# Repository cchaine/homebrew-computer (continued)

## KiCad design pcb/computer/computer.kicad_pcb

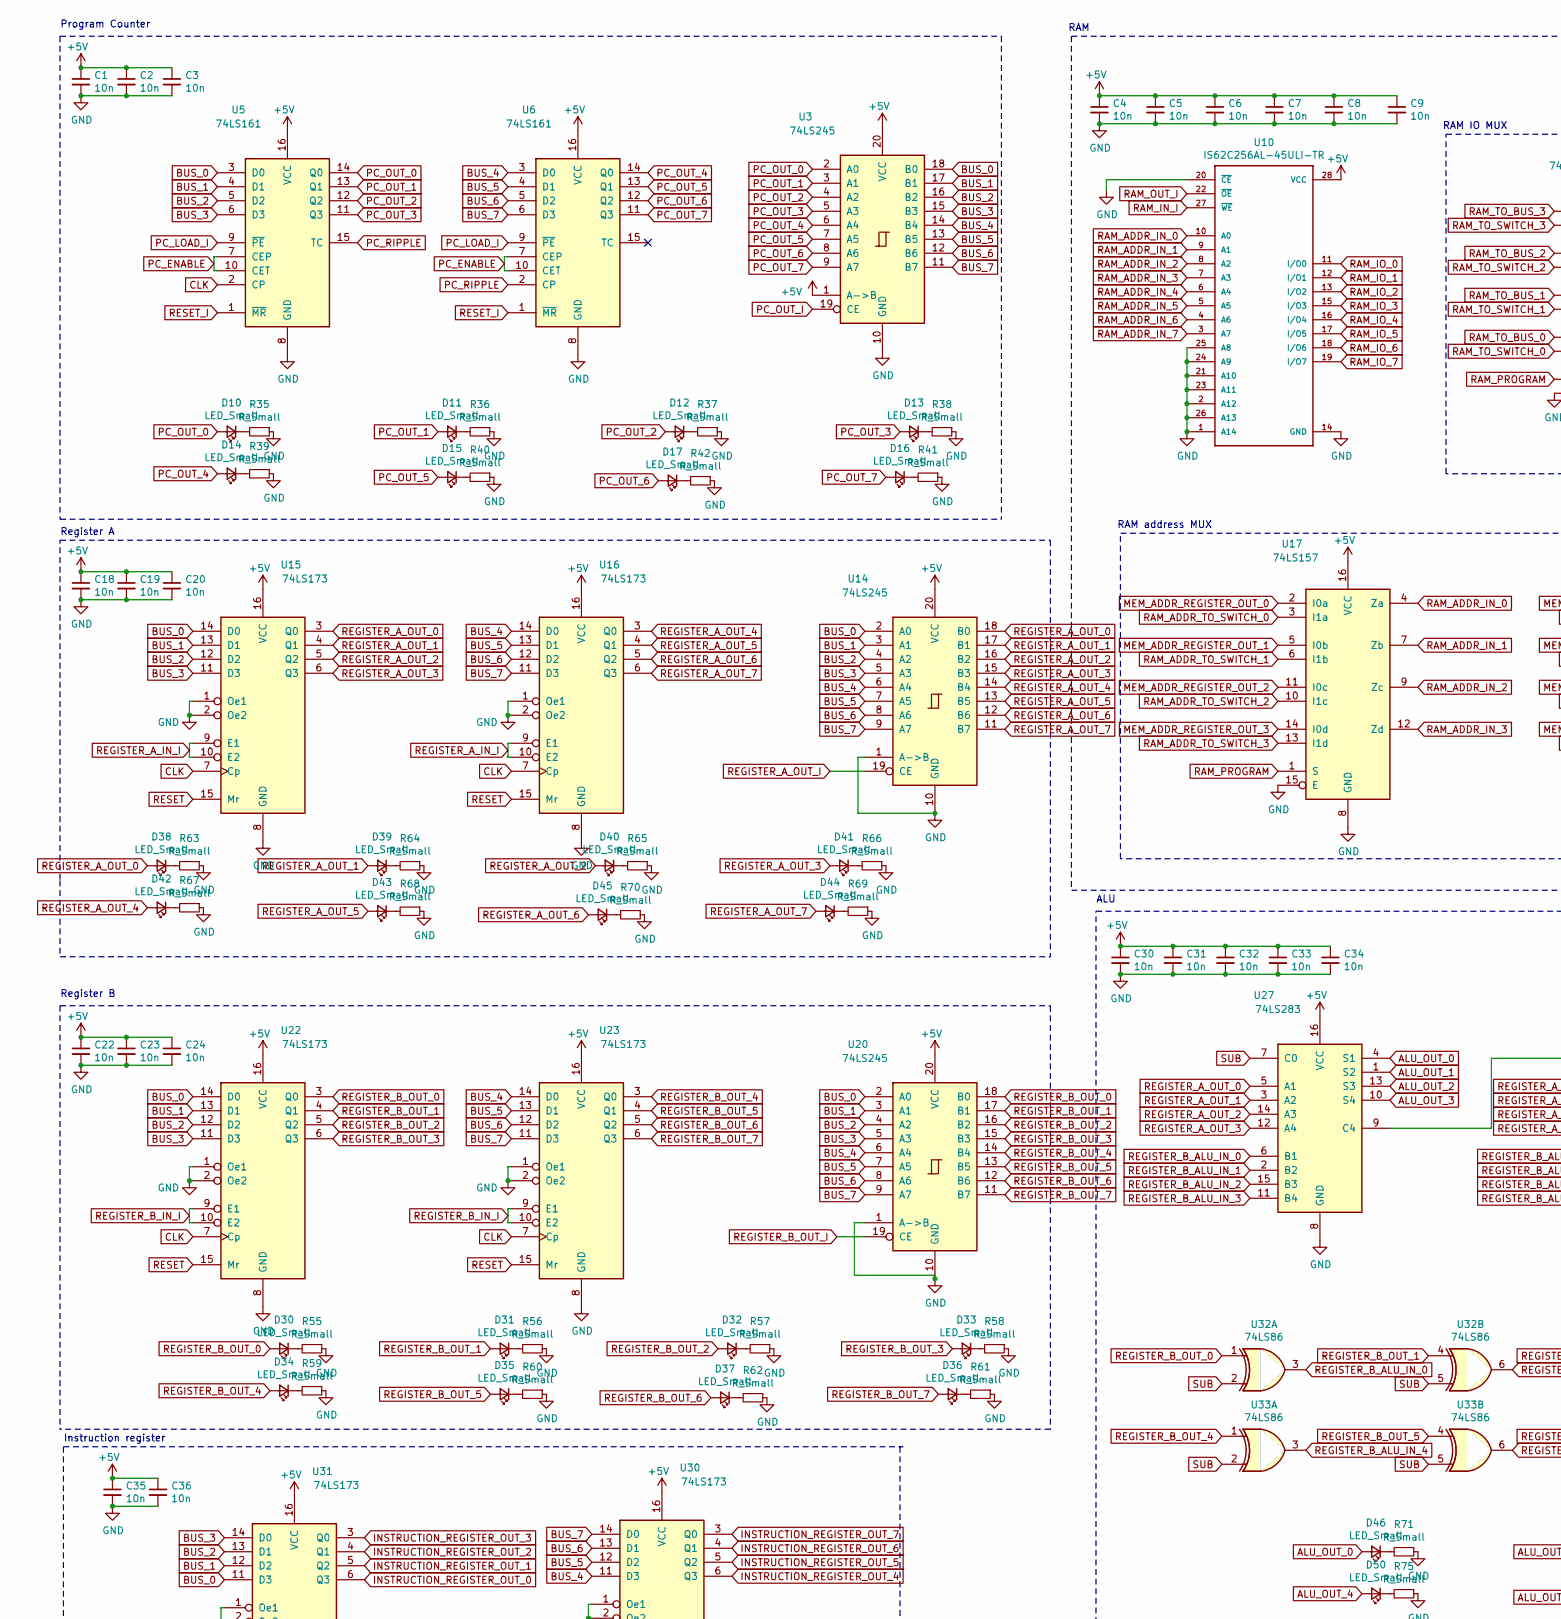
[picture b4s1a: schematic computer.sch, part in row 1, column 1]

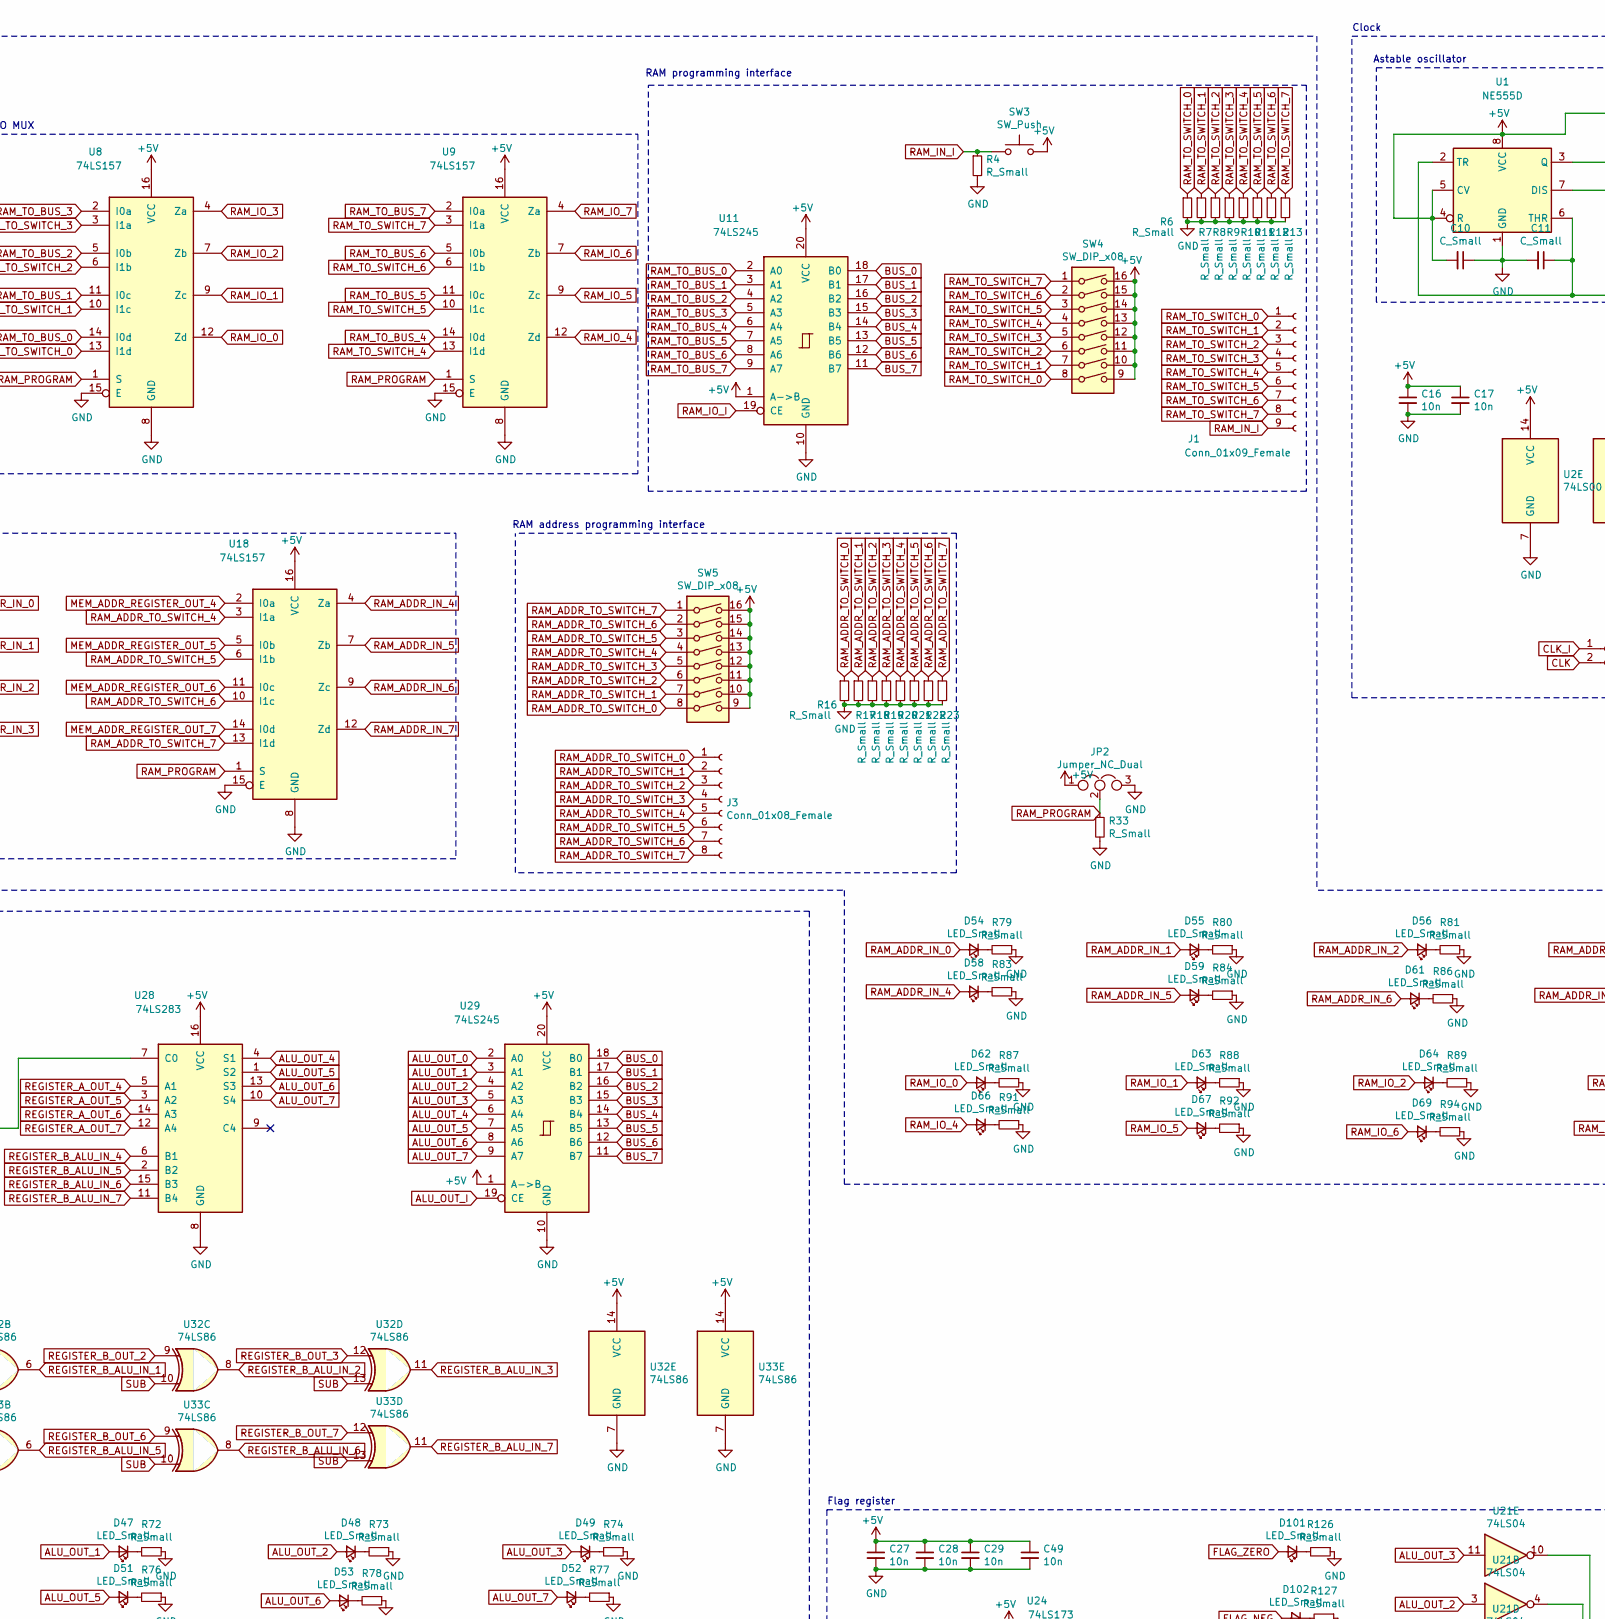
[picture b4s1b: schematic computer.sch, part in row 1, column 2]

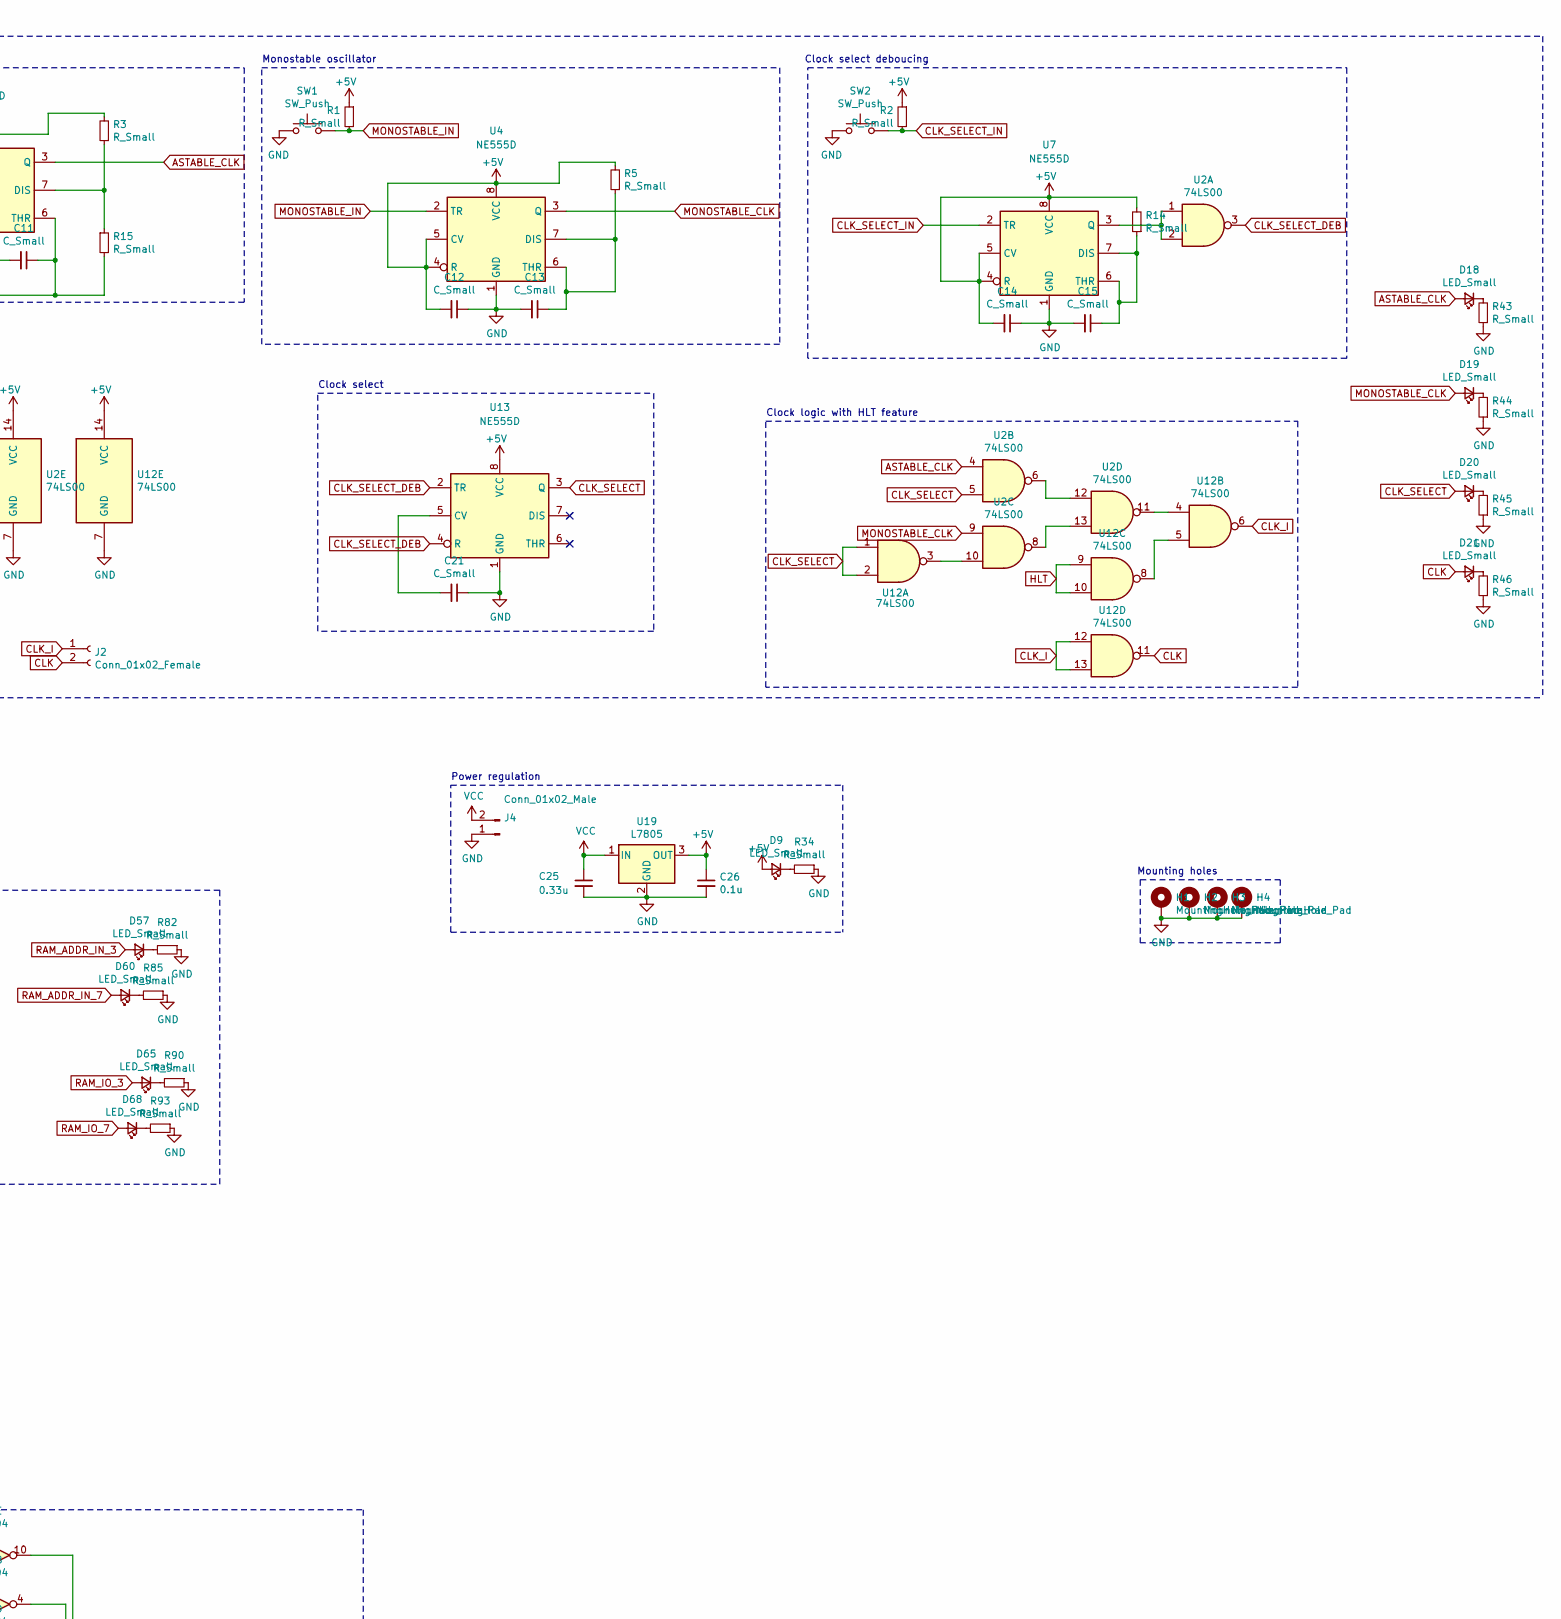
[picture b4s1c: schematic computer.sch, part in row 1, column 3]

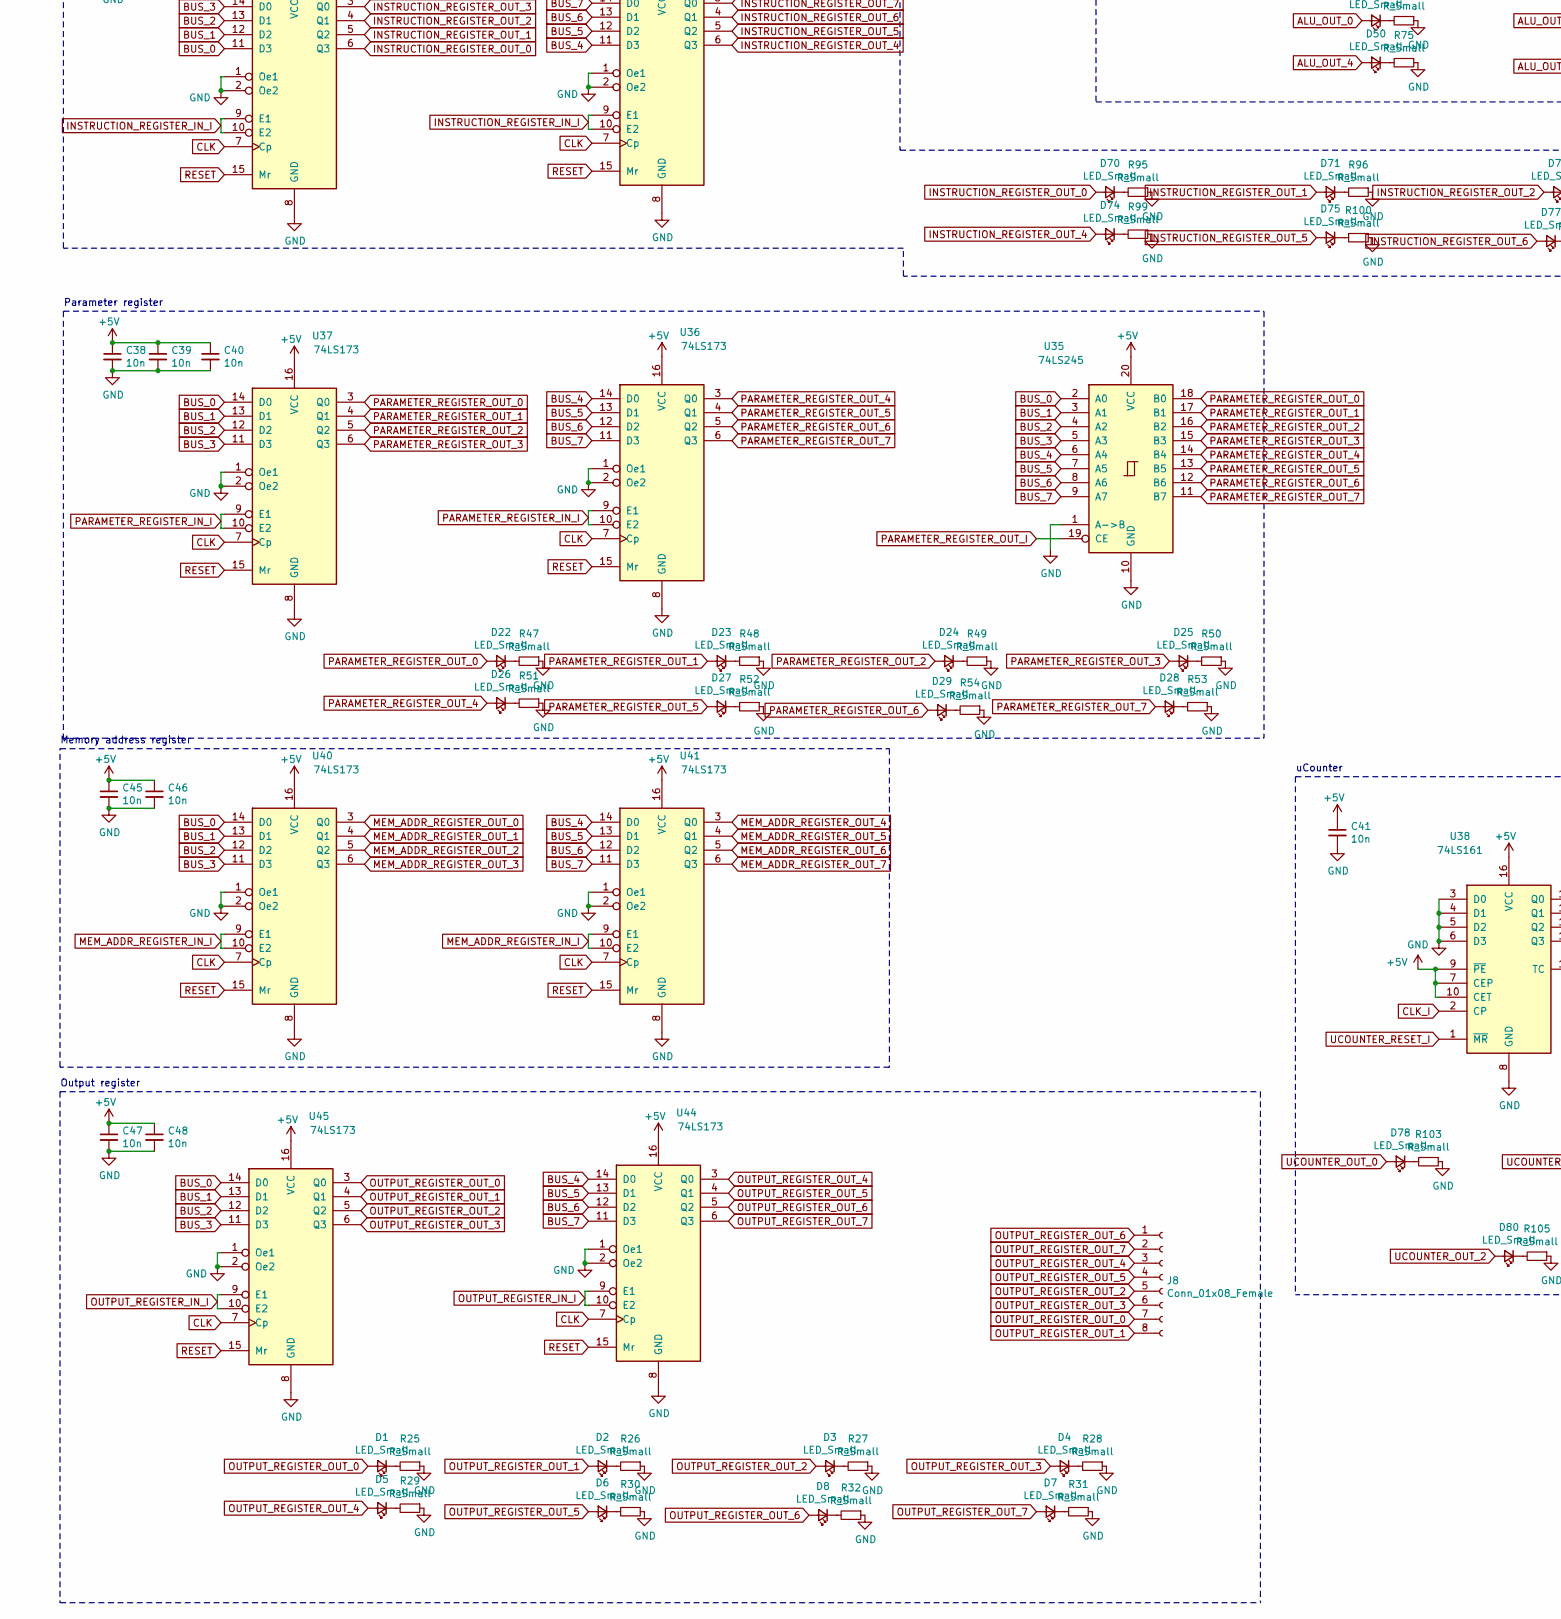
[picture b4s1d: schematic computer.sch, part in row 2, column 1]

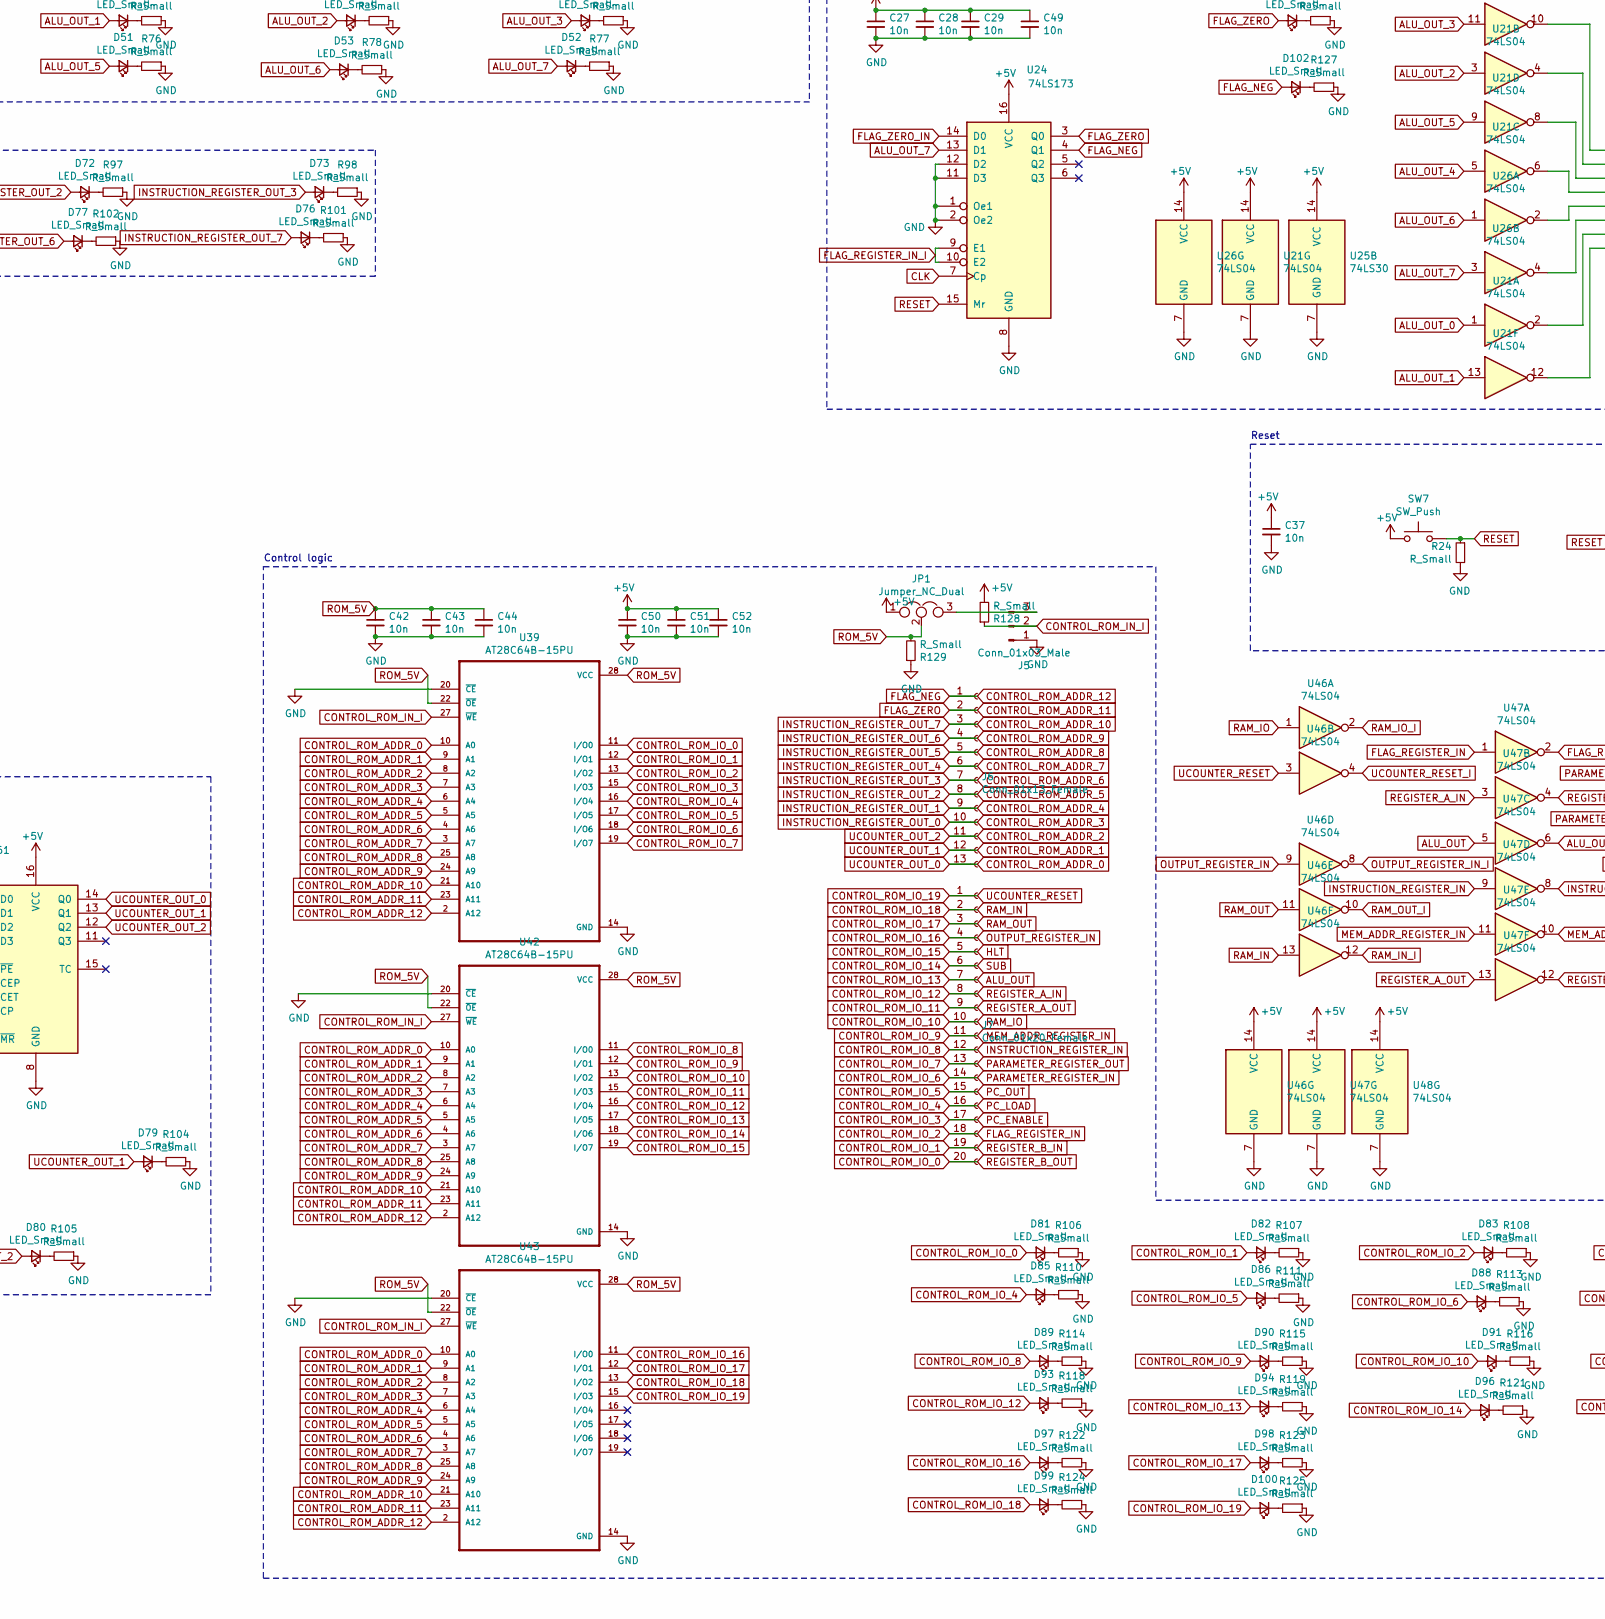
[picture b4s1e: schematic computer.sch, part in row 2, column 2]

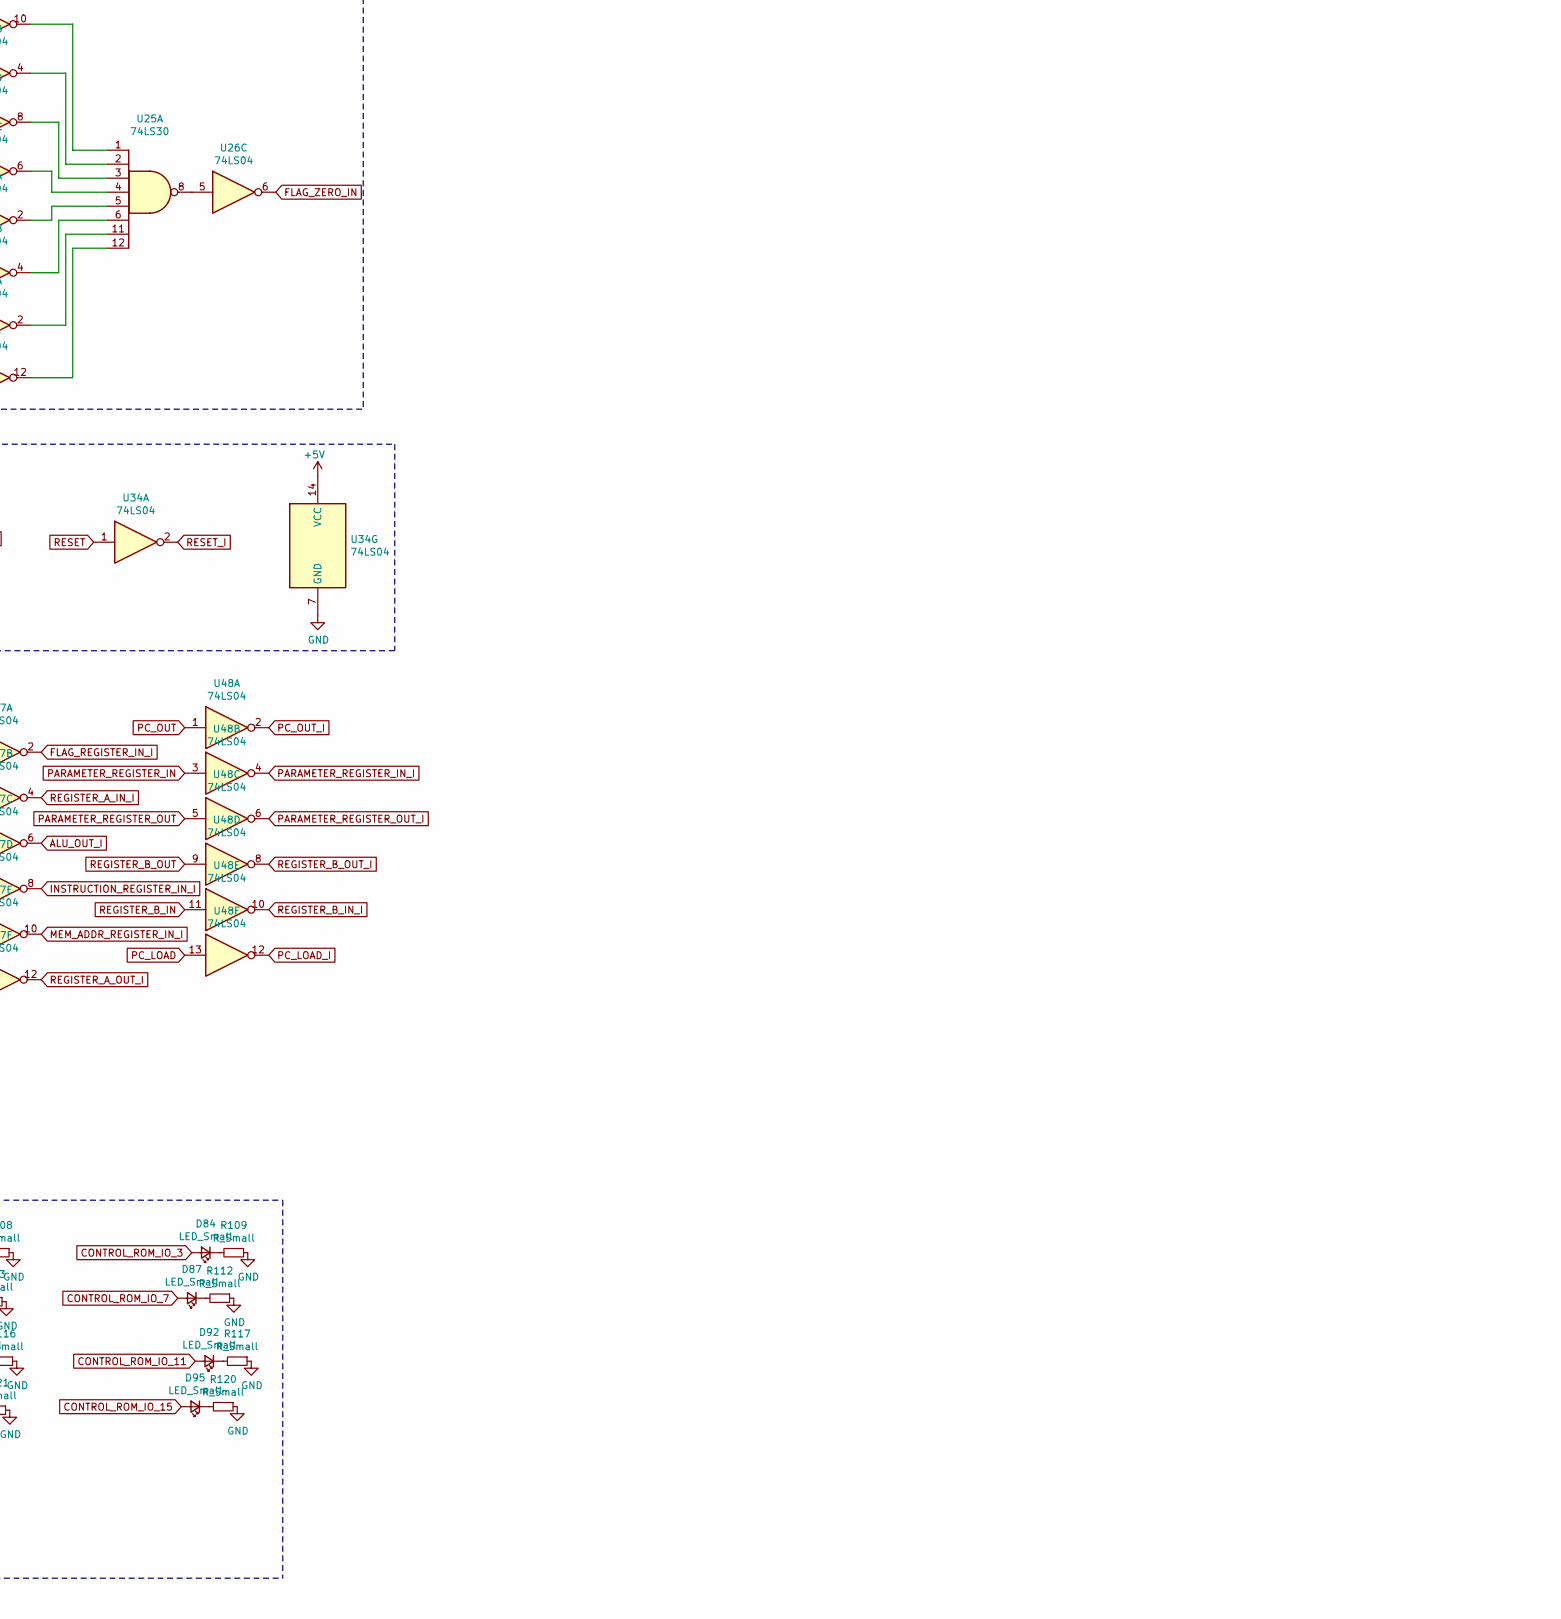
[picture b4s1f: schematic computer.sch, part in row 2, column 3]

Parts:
C1, C2, C3, C4, C5, C6, C7, C8, C9, C16, C17, C18, C19, C20, C22, C23, C24, C27, C28, C29, C30, C31, C32, C33, C34, C35, C36, C37, C38, C39, C40, C41, C42, C43, C44, C45, C46, C47, C48, C49, C50, C51, C52: 10n; C_0603_1608Metric
C10, C11, C12, C13, C14, C15, C21: C_Small; C_0603_1608Metric
C25: 0.33u; C_0603_1608Metric
C26: 0.1u; C_0603_1608Metric
D1, D2, D3, D4, D5, D6, D7, D8, D9, D10, D11, D12, D13, D14, D15, D16, D17, D18, D19, D20, D21, D22, D23, D24, D25, D26, D27, D28, D29, D30, D31, D32, D33, D34, D35, D36, D37, D38, D39, D40, D41, D42, D43, D44, D45, D46, D47, D48, D49, D50, D51, D52, D53, D54, D55, D56, D57, D58, D59, D60, D61, D62, D63, D64, D65, D66, D67, D68, D69, D70, D71, D72, D73, D74, D75, D76, D77, D78, D79, D80, D81, D82, D83, D84, D85, D86, D87, D88, D89, D90, D91, D92, D93, D94, D95, D96, D97, D98, D99, D100, D101, D102: LED_Small; LED_0603_1608Metric
H1, H2, H3, H4: MountingHole_Pad; MountingHole_3.7mm_Pad_Via
J1: Conn_01x09_Female; IDC-Header_2x05_P2.54mm_Vertical
J2: Conn_01x02_Female; PinHeader_1x02_P2.54mm_Vertical
J3, J8: Conn_01x08_Female; IDC-Header_2x04_P2.54mm_Vertical
J4: Conn_01x02_Male; PinHeader_1x02_P2.54mm_Vertical
J5: Conn_01x03_Male; JST_EH_B3B-EH-A_1x03_P2.50mm_Vertical
J6: Conn_01x13_Female; IDC-Header_2x07_P2.54mm_Vertical
J7: Conn_01x20_Female; IDC-Header_2x10_P2.54mm_Vertical
JP1, JP2: Jumper_NC_Dual; PinHeader_1x03_P2.00mm_Vertical
R1, R2, R3, R4, R5, R6, R7, R8, R9, R10, R11, R12, R13, R14, R15, R16, R17, R18, R19, R20, R21, R22, R23, R24, R25, R26, R27, R28, R29, R30, R31, R32, R33, R34, R35, R36, R37, R38, R39, R40, R41, R42, R43, R44, R45, R46, R47, R48, R49, R50, R51, R52, R53, R54, R55, R56, R57, R58, R59, R60, R61, R62, R63, R64, R65, R66, R67, R68, R69, R70, R71, R72, R73, R74, R75, R76, R77, R78, R79, R80, R81, R82, R83, R84, R85, R86, R87, R88, R89, R90, R91, R92, R93, R94, R95, R96, R97, R98, R99, R100, R101, R102, R103, R104, R105, R106, R107, R108, R109, R110, R111, R112, R113, R114, R115, R116, R117, R118, R119, R120, R121, R122, R123, R124, R125, R126, R127, R128, R129: R_Small; R_0603_1608Metric
SW1, SW2, SW3, SW7: SW_Push; SW_SPST_B3U-1000P
SW4, SW5: SW_DIP_x08; SW_DIP_SPSTx08_Slide_6.7x21.88mm_W6.73mm_P2.54mm_LowProfile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
U1: NE555D; SOIC-8_3.9x4.9mm_P1.27mm
U2, U12: 74LS00; SO-14_5.3x10.2mm_P1.27mm
U3, U11, U14, U20, U29, U35: 74LS245; TSSOP-20_4.4x6.5mm_P0.65mm
U4, U7, U13: NE555D; SO-8_3.9x4.9mm_P1.27mm
U5, U6, U38: 74LS161; SOIC-16_3.9x9.9mm_P1.27mm
U8, U9, U17, U18: 74LS157; SOIC-16_3.9x9.9mm_P1.27mm
U10: IS62C256AL-45ULI-TR; SOIC127P1210X305-28N
U15, U16, U22, U23, U24, U30, U31, U36, U37, U40, U41, U44, U45: 74LS173; SOIC127P600X175-16N
U19: L7805; TO-252-3_TabPin2
U21, U26, U34, U46, U47, U48: 74LS04; SOIC-14_3.9x8.7mm_P1.27mm
U25: 74LS30; SOIC-14_3.9x8.7mm_P1.27mm
U27, U28: 74LS283; SOIC127P600X175-16N
U32, U33: 74LS86; SOIC-14_3.9x8.7mm_P1.27mm
U39, U42, U43: AT28C64B-15PU; SOIC127P1030X265-28N

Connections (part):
+5V: C1.1, C2.1, C3.1, C4.1, C5.1, C6.1, C7.1, C8.1, C9.1, C10.2, C12.2, C14.2, C16.1, C17.1, C18.1, C19.1, C20.1, C22.1, C23.1, C24.1, C26.1, C27.1, C28.1, C29.1, C30.1, C31.1, C32.1, C33.1, C34.1, C35.1, C36.1, C37.1, C38.1, C39.1, C40.1, C41.1, C45.1, C46.1, C47.1, C48.1, C49.1, C50.1, C51.1, C52.1, D9.2 (A), JP1.1, JP2.1, R1.1, R2.1, R3.2, R5.2, R14.2, R128.2, SW3.2, SW4.9, SW4.10, SW4.11, SW4.12, SW4.13, SW4.14, SW4.15, SW4.16, SW5.9, SW5.10, SW5.11, SW5.12, SW5.13, SW5.14, SW5.15, SW5.16, SW7.1, U1.4 (R), U1.5 (CV), U1.8 (VCC), U2.14 (VCC), U3.1 (A->B), U3.20 (VCC), U4.4 (R), U4.5 (CV), U4.8 (VCC), U5.16 (VCC), U6.16 (VCC)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
ALU_OUT: D94.2 (A), J7.7, U42.17 (I/O5), U47.5
ALU_OUT_0: D46.2 (A), U21.1, U27.4 (S1), U29.2 (A0)
ALU_OUT_1: D47.2 (A), U21.13, U27.1 (S2), U29.3 (A1)
ALU_OUT_2: D48.2 (A), U21.3, U27.13 (S3), U29.4 (A2)
ALU_OUT_3: D49.2 (A), U21.11, U27.10 (S4), U29.5 (A3)
ALU_OUT_4: D50.2 (A), U21.5, U28.4 (S1), U29.6 (A4)
ALU_OUT_5: D51.2 (A), U21.9, U28.1 (S2), U29.7 (A5)
ALU_OUT_6: D53.2 (A), U26.1, U28.13 (S3), U29.8 (A6)
ALU_OUT_7: D52.2 (A), U24.13 (D1), U26.3, U28.10 (S4), U29.9 (A7)
ALU_OUT_I: U29.19 (CE), U47.6
ASTABLE_CLK: D18.2 (A), U1.3 (Q), U2.4
BUS_0: U3.18 (B0), U5.3 (D0), U11.18 (B0), U14.2 (A0), U15.14 (D0), U20.2 (A0), U22.14 (D0), U29.18 (B0), U31.11 (D3), U35.2 (A0), U37.14 (D0), U40.14 (D0), U45.14 (D0)
BUS_1: U3.17 (B1), U5.4 (D1), U11.17 (B1), U14.3 (A1), U15.13 (D1), U20.3 (A1), U22.13 (D1), U29.17 (B1), U31.12 (D2), U35.3 (A1), U37.13 (D1), U40.13 (D1), U45.13 (D1)
BUS_2: U3.16 (B2), U5.5 (D2), U11.16 (B2), U14.4 (A2), U15.12 (D2), U20.4 (A2), U22.12 (D2), U29.16 (B2), U31.13 (D1), U35.4 (A2), U37.12 (D2), U40.12 (D2), U45.12 (D2)
BUS_3: U3.15 (B3), U5.6 (D3), U11.15 (B3), U14.5 (A3), U15.11 (D3), U20.5 (A3), U22.11 (D3), U29.15 (B3), U31.14 (D0), U35.5 (A3), U37.11 (D3), U40.11 (D3), U45.11 (D3)
BUS_4: U3.14 (B4), U6.3 (D0), U11.14 (B4), U14.6 (A4), U16.14 (D0), U20.6 (A4), U23.14 (D0), U29.14 (B4), U30.11 (D3), U35.6 (A4), U36.14 (D0), U41.14 (D0), U44.14 (D0)
BUS_5: U3.13 (B5), U6.4 (D1), U11.13 (B5), U14.7 (A5), U16.13 (D1), U20.7 (A5), U23.13 (D1), U29.13 (B5), U30.12 (D2), U35.7 (A5), U36.13 (D1), U41.13 (D1), U44.13 (D1)
BUS_6: U3.12 (B6), U6.5 (D2), U11.12 (B6), U14.8 (A6), U16.12 (D2), U20.8 (A6), U23.12 (D2), U29.12 (B6), U30.13 (D1), U35.8 (A6), U36.12 (D2), U41.12 (D2), U44.12 (D2)
BUS_7: U3.11 (B7), U6.6 (D3), U11.11 (B7), U14.9 (A7), U16.11 (D3), U20.9 (A7), U23.11 (D3), U29.11 (B7), U30.14 (D0), U35.9 (A7), U36.11 (D3), U41.11 (D3), U44.11 (D3)
CLK: D21.2 (A), J2.2, U5.2 (CP), U12.11, U15.7 (Cp), U16.7 (Cp), U22.7 (Cp), U23.7 (Cp), U24.7 (Cp), U30.7 (Cp), U31.7 (Cp), U36.7 (Cp), U37.7 (Cp), U40.7 (Cp), U41.7 (Cp), U44.7 (Cp), U45.7 (Cp)
CLK_I: J2.1, U12.6, U12.12, U12.13, U38.2 (CP)
CLK_SELECT: D20.2 (A), U2.5, U12.1, U12.2, U13.3 (Q)
CLK_SELECT_DEB: U2.3, U13.2 (TR), U13.4 (R)
CLK_SELECT_IN: R2.2, SW2.2, U7.2 (TR)
CONTROL_ROM_ADDR_0: D78.2 (A), J6.13, U38.14 (Q0), U39.10 (A0), U42.10 (A0), U43.10 (A0)
CONTROL_ROM_ADDR_1: D79.2 (A), J6.12, U38.13 (Q1), U39.9 (A1), U42.9 (A1), U43.9 (A1)
CONTROL_ROM_ADDR_2: D80.2 (A), J6.11, U38.12 (Q2), U39.8 (A2), U42.8 (A2), U43.8 (A2)
CONTROL_ROM_ADDR_3: D70.2 (A), J6.10, U31.6 (Q3), U39.7 (A3), U42.7 (A3), U43.7 (A3)
CONTROL_ROM_ADDR_4: D71.2 (A), J6.9, U31.5 (Q2), U39.6 (A4), U42.6 (A4), U43.6 (A4)
CONTROL_ROM_ADDR_5: D72.2 (A), J6.8, U31.4 (Q1), U39.5 (A5), U42.5 (A5), U43.5 (A5)
CONTROL_ROM_ADDR_6: D73.2 (A), J6.7, U31.3 (Q0), U39.4 (A6), U42.4 (A6), U43.4 (A6)
CONTROL_ROM_ADDR_7: D74.2 (A), J6.6, U30.6 (Q3), U39.3 (A7), U42.3 (A7), U43.3 (A7)
CONTROL_ROM_ADDR_8: D75.2 (A), J6.5, U30.5 (Q2), U39.25 (A8), U42.25 (A8), U43.25 (A8)
CONTROL_ROM_ADDR_9: D77.2 (A), J6.4, U30.4 (Q1), U39.24 (A9), U42.24 (A9), U43.24 (A9)
CONTROL_ROM_ADDR_10: D76.2 (A), J6.3, U30.3 (Q0), U39.21 (A10), U42.21 (A10), U43.21 (A10)
CONTROL_ROM_ADDR_11: D101.2 (A), J6.2, U24.3 (Q0), U39.23 (A11), U42.23 (A11), U43.23 (A11)
CONTROL_ROM_ADDR_12: D102.2 (A), J6.1, U24.4 (Q1), U39.2 (A12), U42.2 (A12), U43.2 (A12)
CONTROL_ROM_IN_I: J5.2, R128.1, U39.27 (~WE~), U42.27 (~WE~), U43.27 (~WE~)
CONTROL_ROM_IO_0: D81.2 (A), J7.20, U39.11 (I/O0), U48.9
CONTROL_ROM_IO_1: D82.2 (A), J7.19, U39.12 (I/O1), U48.11
CONTROL_ROM_IO_2: D83.2 (A), J7.18, U39.13 (I/O2), U47.1
CONTROL_ROM_IO_3: D84.2 (A), J7.17, U5.7 (CEP), U5.10 (CET), U6.7 (CEP), U6.10 (CET), U39.15 (I/O3)
CONTROL_ROM_IO_4: D85.2 (A), J7.16, U39.16 (I/O4), U48.13
CONTROL_ROM_IO_5: D86.2 (A), J7.15, U39.17 (I/O5), U48.1
CONTROL_ROM_IO_6: D88.2 (A), J7.14, U39.18 (I/O6), U48.3
CONTROL_ROM_IO_7: D87.2 (A), J7.13, U39.19 (I/O7), U48.5
CONTROL_ROM_IO_8: D89.2 (A), J7.12, U42.11 (I/O0), U47.9
CONTROL_ROM_IO_9: D90.2 (A), J7.11, U42.12 (I/O1), U47.11
CONTROL_ROM_IO_10: D91.2 (A), J7.10, U42.13 (I/O2), U46.1
CONTROL_ROM_IO_11: D92.2 (A), J7.9, U42.15 (I/O3), U47.13
CONTROL_ROM_IO_12: D93.2 (A), J7.8, U42.16 (I/O4), U47.3
CONTROL_ROM_IO_14: D96.2 (A), J7.6, U27.7 (C0), U32.2, U32.5, U32.10, U32.13, U33.2, U33.5, U33.10, U33.13, U42.18 (I/O6)
CONTROL_ROM_IO_15: D95.2 (A), J7.5, U12.9, U12.10, U42.19 (I/O7)
CONTROL_ROM_IO_16: D97.2 (A), J7.4, U43.11 (I/O0), U46.9
CONTROL_ROM_IO_17: D98.2 (A), J7.3, U43.12 (I/O1), U46.11
CONTROL_ROM_IO_18: D99.2 (A), J7.2, U43.13 (I/O2), U46.13
CONTROL_ROM_IO_19: D100.2 (A), J7.1, U43.15 (I/O3), U46.3
FLAG_REGISTER_IN_I: U24.9 (E1), U24.10 (E2), U47.2
FLAG_ZERO_IN: U24.14 (D0), U26.6
GND: C1.2, C2.2, C3.2, C4.2, C5.2, C6.2, C7.2, C8.2, C9.2, C10.1, C11.2, C12.1, C13.2, C14.1, C15.2, C16.2, C17.2, C18.2, C19.2, C20.2, C21.1, C22.2, C23.2, C24.2, C25.2, C26.2, C27.2, C28.2, C29.2, C30.2, C31.2, C32.2, C33.2, C34.2, C35.2, C36.2, C37.2, C38.2, C39.2, C40.2, C41.2, C42.2, C43.2, C44.2, C45.2, C46.2, C47.2, C48.2, C49.2, C50.2, C51.2, C52.2, H1.1, H2.1, H3.1, H4.1, J4.1, J5.1, JP2.3, R4.2, R6.2, R7.2, R8.2, R9.2, R10.2, R11.2, R12.2, R13.2, R16.2, R17.2, R18.2, R19.2, R20.2, R21.2, R22.2, R23.2, R24.2, R25.1, R26.1, R27.1, R28.1, R29.1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
INSTRUCTION_REGISTER_IN_I: U30.9 (E1), U30.10 (E2), U31.9 (E1), U31.10 (E2), U47.8
MEM_ADDR_REGISTER_IN_I: U40.9 (E1), U40.10 (E2), U41.9 (E1), U41.10 (E2), U47.10
MEM_ADDR_REGISTER_OUT_0: U17.2 (I0a), U40.3 (Q0)
MEM_ADDR_REGISTER_OUT_1: U17.5 (I0b), U40.4 (Q1)
MEM_ADDR_REGISTER_OUT_2: U17.11 (I0c), U40.5 (Q2)
MEM_ADDR_REGISTER_OUT_3: U17.14 (I0d), U40.6 (Q3)
MEM_ADDR_REGISTER_OUT_4: U18.2 (I0a), U41.3 (Q0)
MEM_ADDR_REGISTER_OUT_5: U18.5 (I0b), U41.4 (Q1)
MEM_ADDR_REGISTER_OUT_6: U18.11 (I0c), U41.5 (Q2)
MEM_ADDR_REGISTER_OUT_7: U18.14 (I0d), U41.6 (Q3)
MONOSTABLE_CLK: D19.2 (A), U2.9, U4.3 (Q)
MONOSTABLE_IN: R1.2, SW1.2, U4.2 (TR)
unnamed: C11.1, R15.2, U1.2 (TR), U1.6 (THR)
unnamed: C13.1, R5.1, U4.6 (THR), U4.7 (DIS)
unnamed: C15.1, R14.1, U7.6 (THR), U7.7 (DIS)
unnamed: C21.2, U13.5 (CV)
unnamed: D1.1 (K), R25.2
unnamed: D2.1 (K), R26.2
unnamed: D3.1 (K), R27.2
unnamed: D4.1 (K), R28.2
unnamed: D5.1 (K), R29.2
unnamed: D6.1 (K), R30.2
unnamed: D7.1 (K), R31.2
unnamed: D8.1 (K), R32.2
unnamed: D9.1 (K), R34.2
unnamed: D10.1 (K), R35.2
unnamed: D11.1 (K), R36.2
unnamed: D12.1 (K), R37.2
unnamed: D13.1 (K), R38.2
unnamed: D14.1 (K), R39.2
unnamed: D15.1 (K), R40.2
unnamed: D16.1 (K), R41.2
unnamed: D17.1 (K), R42.2
unnamed: D18.1 (K), R43.2
unnamed: D19.1 (K), R44.2
unnamed: D20.1 (K), R45.2
unnamed: D21.1 (K), R46.2
unnamed: D22.1 (K), R47.2
unnamed: D23.1 (K), R48.2
unnamed: D24.1 (K), R49.2
unnamed: D25.1 (K), R50.2
unnamed: D26.1 (K), R51.2
unnamed: D27.1 (K), R52.2
unnamed: D28.1 (K), R53.2
unnamed: D29.1 (K), R54.2
unnamed: D30.1 (K), R55.2
unnamed: D31.1 (K), R56.2
unnamed: D32.1 (K), R57.2
unnamed: D33.1 (K), R58.2
unnamed: D34.1 (K), R59.2
unnamed: D35.1 (K), R60.2
unnamed: D36.1 (K), R61.2
unnamed: D37.1 (K), R62.2
unnamed: D38.1 (K), R63.2
unnamed: D39.1 (K), R64.2
unnamed: D40.1 (K), R65.2
unnamed: D41.1 (K), R66.2
unnamed: D42.1 (K), R67.2
unnamed: D43.1 (K), R68.2
unnamed: D44.1 (K), R69.2
unnamed: D45.1 (K), R70.2
unnamed: D46.1 (K), R71.2
unnamed: D47.1 (K), R72.2
unnamed: D48.1 (K), R73.2
unnamed: D49.1 (K), R74.2
unnamed: D50.1 (K), R75.2
unnamed: D51.1 (K), R76.2
unnamed: D52.1 (K), R77.2
unnamed: D53.1 (K), R78.2
unnamed: D54.1 (K), R79.2
unnamed: D55.1 (K), R80.2
unnamed: D56.1 (K), R81.2
unnamed: D57.1 (K), R82.2
unnamed: D58.1 (K), R83.2
unnamed: D59.1 (K), R84.2
unnamed: D60.1 (K), R85.2
unnamed: D61.1 (K), R86.2
unnamed: D62.1 (K), R87.2
unnamed: D63.1 (K), R88.2
unnamed: D64.1 (K), R89.2
unnamed: D65.1 (K), R90.2
unnamed: D66.1 (K), R91.2
unnamed: D67.1 (K), R92.2
unnamed: D68.1 (K), R93.2
unnamed: D69.1 (K), R94.2
unnamed: D70.1 (K), R95.2
unnamed: D71.1 (K), R96.2
unnamed: D72.1 (K), R97.2
unnamed: D73.1 (K), R98.2
unnamed: D74.1 (K), R99.2
unnamed: D75.1 (K), R100.2
unnamed: D76.1 (K), R101.2
unnamed: D77.1 (K), R102.2
unnamed: D78.1 (K), R103.2
unnamed: D79.1 (K), R104.2
unnamed: D80.1 (K), R105.2
unnamed: D81.1 (K), R106.2
unnamed: D82.1 (K), R107.2
unnamed: D83.1 (K), R108.2
unnamed: D84.1 (K), R109.2
unnamed: D85.1 (K), R110.2
unnamed: D86.1 (K), R111.2
unnamed: D87.1 (K), R112.2
unnamed: D88.1 (K), R113.2
unnamed: D89.1 (K), R114.2
unnamed: D90.1 (K), R115.2
unnamed: D91.1 (K), R116.2
unnamed: D92.1 (K), R117.2
unnamed: D93.1 (K), R118.2
unnamed: D94.1 (K), R119.2
unnamed: D95.1 (K), R120.2
unnamed: D96.1 (K), R121.2
unnamed: D97.1 (K), R122.2
unnamed: D98.1 (K), R123.2
unnamed: D99.1 (K), R124.2
unnamed: D100.1 (K), R125.2
unnamed: D101.1 (K), R126.2
unnamed: D102.1 (K), R127.2
unnamed: J5.3, JP1.3
unnamed: R3.1, R15.1, U1.7 (DIS)
unnamed: U2.1, U2.2, U7.3 (Q)
unnamed: U2.6, U2.12
unnamed: U2.8, U2.13
unnamed: U2.10, U12.3
unnamed: U2.11, U12.4
unnamed: U12.5, U12.8
unnamed: U21.2, U25.11
unnamed: U21.4, U25.2
unnamed: U21.6, U25.4
unnamed: U21.8, U25.3
unnamed: U21.10, U25.1
unnamed: U21.12, U25.12
unnamed: U25.5, U26.2
unnamed: U25.6, U26.4
unnamed: U25.8, U26.5
unnamed: U27.9 (C4), U28.7 (C0)
OUTPUT_REGISTER_IN_I: U44.9 (E1), U44.10 (E2), U45.9 (E1), U45.10 (E2), U46.8
OUTPUT_REGISTER_OUT_0: D1.2 (A), J8.7, U45.3 (Q0)
OUTPUT_REGISTER_OUT_1: D2.2 (A), J8.8, U45.4 (Q1)
OUTPUT_REGISTER_OUT_2: D3.2 (A), J8.5, U45.5 (Q2)
OUTPUT_REGISTER_OUT_3: D4.2 (A), J8.6, U45.6 (Q3)
OUTPUT_REGISTER_OUT_4: D5.2 (A), J8.3, U44.3 (Q0)
OUTPUT_REGISTER_OUT_5: D6.2 (A), J8.4, U44.4 (Q1)
OUTPUT_REGISTER_OUT_6: D8.2 (A), J8.1, U44.5 (Q2)
OUTPUT_REGISTER_OUT_7: D7.2 (A), J8.2, U44.6 (Q3)
PARAMETER_REGISTER_IN_I: U36.9 (E1), U36.10 (E2), U37.9 (E1), U37.10 (E2), U48.4
PARAMETER_REGISTER_OUT_0: D22.2 (A), U35.18 (B0), U37.3 (Q0)
PARAMETER_REGISTER_OUT_1: D23.2 (A), U35.17 (B1), U37.4 (Q1)
PARAMETER_REGISTER_OUT_2: D24.2 (A), U35.16 (B2), U37.5 (Q2)
PARAMETER_REGISTER_OUT_3: D25.2 (A), U35.15 (B3), U37.6 (Q3)
PARAMETER_REGISTER_OUT_4: D26.2 (A), U35.14 (B4), U36.3 (Q0)
PARAMETER_REGISTER_OUT_5: D27.2 (A), U35.13 (B5), U36.4 (Q1)
PARAMETER_REGISTER_OUT_6: D29.2 (A), U35.12 (B6), U36.5 (Q2)
PARAMETER_REGISTER_OUT_7: D28.2 (A), U35.11 (B7), U36.6 (Q3)
PARAMETER_REGISTER_OUT_I: U35.19 (CE), U48.6
PC_LOAD_I: U5.9 (~PE), U6.9 (~PE), U48.12
PC_OUT_0: D10.2 (A), U3.2 (A0), U5.14 (Q0)
PC_OUT_1: D11.2 (A), U3.3 (A1), U5.13 (Q1)
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
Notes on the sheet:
Parameter register
Instruction register
Register B
Register A
Program Counter
Clock
Clock logic with HLT feature
Clock select
Clock select deboucing
Monostable oscillator
Astable oscillator
Power regulation
Flag register
Reset
RAM programming interface
RAM address programming interface
ALU
RAM address MUX
RAM IO MUX
RAM
Mounting holes
Output register
Memory address register
uCounter
Control logic
